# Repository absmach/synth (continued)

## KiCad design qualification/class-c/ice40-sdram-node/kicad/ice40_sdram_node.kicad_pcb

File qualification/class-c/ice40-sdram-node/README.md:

# iCE40HX4K SDR SDRAM node with a USB-C power input (Class C, case 2)

An iCE40HX4K FPGA in a 144-pin TQFP (0.5 mm pitch) with a 64 Mbit SDR SDRAM (ISSI IS42S16400J, TSOP-II-54), an SPI boot flash, a 1x6 programming header and three status LEDs. A USB-C receptacle (5 V only) powers it. The board has six copper layers and measures 70.0 x 61.0 mm.

It answers #329 under #40: a board whose memory interface is length- and impedance-sensitive, made by an agent driving `synth mcp`. A soft controller in the FPGA fabric drives a single-data-rate SDRAM, so there is no DQS strobe, no differential pair and no DDR claim. Case 2 is claimed for the routing of the memory lines (length, skew, impedance) only. No controller or bitstream has run on the board, so no interface timing (setup, hold, 143 MHz operation) is claimed.

The prompt to reproduce the board is in [`PROMPT.md`](PROMPT.md), written from the finished board. The prompts the agent ran are in the history at `9f458a8d`.

## The board

### Parts

| Group         | Parts                                                                                                                                                              |
| ------------- | ------------------------------------------------------------------------------------------------------------------------------------------------------------------ |
| Power entry   | `J1` Korean Hroparts TYPE-C-31-M-12 USB-C receptacle. It takes 5 V from VBUS only. D+, D- and SBU are unconnected.                                                 |
| Power entry   | `R2` and `R3`, 5.1 k pull-downs on CC1 and CC2.                                                                                                                    |
| Power entry   | `F1` Bourns MF-MSMF110/16-2 (1.1 A hold, 2.2 A trip, 16 V).                                                                                                        |
| Power entry   | `D1` Nexperia PTVS6V0S1UR (6.0 V standoff, 6.67 V minimum breakdown), above the 5.25 V maximum input, and `C1`.                                                    |
| Power entry   | No reverse-polarity stage. A Type-C receptacle cannot be mated reversed.                                                                                           |
| 3.3 V         | `U1` Diodes AP7361C-33E-13 low-dropout regulator (1 A, 360 mV typical dropout at 1 A, SOT-223, stable with ceramic capacitors) with 10 uF capacitors `C2` to `C5`. |
| 3.3 V         | `R_SURGE`, a 1 ohm series resistor (Yageo RC1206FR-071RL, 250 mW) that keeps a clamp event of `D1` off the regulator input.                                        |
| 1.2 V core    | `U2` Texas Instruments TLV70012DDCR, TSOT-23-5, with `C6` and `C7`.                                                                                                |
| 1.2 V core    | The PLL supply `VCCPLL` runs through the ferrite bead `L1` (Murata BLM18AG601SN1D) and `C23`.                                                                      |
| FPGA          | `U3` Lattice iCE40HX4K-TQ144 with 100 nF supply decoupling `C10` to `C24`.                                                                                         |
| FPGA          | `X1`, a 25 MHz oscillator on global buffer input `GBIN1` (`iot_197_gbin1`) with `C41`. The iCE40HX has no internal oscillator.                                     |
| FPGA          | `RCB1` and `RCB2` pull `CBSEL0` and `CBSEL1` down.                                                                                                                 |
| SDRAM         | `U4` ISSI IS42S16400J-7TLI (64 Mbit, 143 MHz, 3.0 to 3.6 V) with decoupling `C30` to `C37`.                                                                        |
| SDRAM         | Six 22 ohm series resistors `RS1` to `RS6` at the FPGA end of the command, clock and control lines.                                                                |
| SDRAM         | `RPD1` to `RPD8`, one 10 k resistor from each of `DQ0` to `DQ7` to ground.                                                                                         |
| Configuration | `U5` Winbond W25Q128JVSIQ, SOIC-8 208 mil, master SPI.                                                                                                             |
| Configuration | `R10` and `R11` pull `CRESET_B` and `CDONE` up. `R12` pulls up the chip select. `R13` and `R14` pull up the write-protect and hold pins.                           |
| Configuration | `J2` 1x6 programming header (SS_B, SCK, SDI, SDO, CRESET_B, GND).                                                                                                  |
| Protection    | `D6` and `D7` TPD1E10B06 bidirectional TVS diodes, one on each CC line at the receptacle, with no rail connection.                                                 |
| Indicators    | `D2` red (3.3 V present).                                                                                                                                          |
| Indicators    | `D3` green (CDONE), buffered by the N-MOSFET `Q2` AO3400A because CDONE is open-drain.                                                                             |
| Indicators    | `D4` green user LED.                                                                                                                                               |
| Mechanical    | Test points `TP1` to `TP7`, all on the bottom side of the board. `TP1` to `TP6` sit in a row 1.3 mm from the bottom edge.                                                                                                                                        |
| Mechanical    | Two M2.5 mounting holes `H1` and `H2` at opposite corners, each 4.0 mm from its two board edges.                                                                                                         |

### Layout

| Item                    | Value                                                                                                                                                                                         |
| ----------------------- | --------------------------------------------------------------------------------------------------------------------------------------------------------------------------------------------- |
| Outline                 | 70.0 x 61.0 mm                                                                                                                                                                                |
| Copper layers           | 6                                                                                                                                                                                             |
| Stackup                 | JLCPCB `JLC06161H-3313`: prepreg 3313 0.0994 mm er 4.1, core 0.55 mm er 4.6, prepreg 2116 0.1088 mm er 4.16. Outer copper 35 um, inner 15.2 um. The board is 1.47 mm thick in the STEP model. |
| Parts in the BOM        | 85 lines: 76 parts plus 2 mounting holes and 7 test points, which are board features with no part                                                                                             |
| Parts placed in the CPL | 76                                                                                                                                                                                            |
| Nets                    | 69, all 69 routed                                                                                                                                                                             |
| Track segments          | 913                                                                                                                                                                                           |
| Vias                    | 197: 78 of 0.46/0.2 mm and 119 of 0.6/0.3 mm                                                                                                                                                  |
| Track length            | 1874.2 mm                                                                                                                                                                                     |
| Zones and planes        | A `GND` zone on all six layers. Supply nets are routed as tracks.                                                                                                                             |
| Fab package             | `fab/gerbers.zip` (18 files: 13 Gerber layers, two drill files, two drill maps and the job file), `fab/bom.csv` and `fab/cpl.csv`                                                             |
| 3D models               | `models/` holds the STEP body of every part the board references and the board model `ice40_sdram_node.step`. KiCad's library has no model for `J1` or `X1`. `J1` uses the HRO TYPE-C-31-M-12 STEP from github.com/ai03-2725/Type-C.pretty (the repository states no licence), placed to match KiCad's footprint. `X1` is a simplified box of its envelope. The mounting holes have no body. The board file reaches the models by the relative path `${KIPRJMOD}/../models/`. |
| Schematic               | `images/schematic.pdf`: 11 vector pages, one per sheet, plotted by `kicad-cli sch export pdf`.                                                                                                               |

### Checks

| Check                               | Result                               | Notes                                                                                                                                                                         |
| ----------------------------------- | ------------------------------------ | ----------------------------------------------------------------------------------------------------------------------------------------------------------------------------- |
| KiCad DRC (10.0.8, --refill-zones)  | 0 errors, 1 warning, 0 unconnected  | The warning is a `via_dangling` on a `CRESET_B` via beside `TP6`. The DRC without `--refill-zones` reports the same.                                                                                                 |
| KiCad ERC (10.0.8)                  | 0 errors, 18 warnings, 0 unconnected | 17 `lib_symbol_issues` and 1 `lib_symbol_mismatch` warnings.                                                                                                                  |
| Gerbers plotted from refilled zones | Yes                                  | The committed board carries refilled zones, and the Gerbers are plotted from that fill.                                                                                       |
| Routing                             | 69 of 69 nets routed                 | KiCadRoutingTools `9399bfb2`.                                                                                                                                                 |
| Routing engine policy               | `engine_policy_verdict: rejected`    | Its strict-size policy rejects any track or via narrower than its net class. Its counters claim 172 vias and 0 in pads. The Layout counts are taken from the delivered board. |
| Synth validate                      | No errors                            | It reports `W-SYNTH-THERMAL-001` on `Q2`. The check applies the generic AO3400A package rating to an LED switch, not a real load.                                             |
| Class skew check `E-SYNTH-DRC-019`  | Not run                              | Synth's export gate does not run it (#147). The skew figures below are measured on the delivered board.                                                                       |

### Design figures

| Area             | Item                                               | Value                                                                                                                                                                                                                                    | Basis                                                      |
| ---------------- | -------------------------------------------------- | ---------------------------------------------------------------------------------------------------------------------------------------------------------------------------------------------------------------------------------------- | ---------------------------------------------------------- |
| FPGA             | User I/O                                           | 107                                                                                                                                                                                                                                      | Lattice DS1040                                             |
| FPGA             | Part model                                         | [`registry/parts/fpga/ice40hx4k_tq144.synth.toml`](../../../registry/parts/fpga/ice40hx4k_tq144.synth.toml), built from KiCad's `FPGA_Lattice:ICE40HX4K-TQ144` symbol with the pin functions of DS1040                                   | Lattice DS1040                                             |
| FPGA             | `GNDPLL` pins `gndpll0` and `gndpll1` | Left unconnected. Lattice DS1040 v3.4, Signal Descriptions: the PLL ground connection is made on the FPGA, so `GNDPLL` must not be connected to the board ground. The PLL is not used. | Lattice DS1040 v3.4 |
| Placement        | Memory pins                                        | The memory pins sit on the FPGA's left side facing the SDRAM, in the order of the SDRAM's near pin row. The data bus runs straight across with no crossings.                                                                             | measured on the board file                                 |
| Signal integrity | Address and command skew                           | 57.6 mm, limit `max_skew` 60 mm                                                                                                                                                                                                          | measured on the board file                                 |
| Signal integrity | Longest address or command net                     | `SD_RAS`, 68.6 mm across both nets of its series resistor, limit `max_length` 80 mm                                                                                                                                                       | measured on the board file                                 |
| Signal integrity | Shortest address or command net                    | `SD_A7`, 11.0 mm                                                                                                                                                                                                                        | measured on the board file                                 |
| Signal integrity | Data bus spread                                    | 6.3 mm, limit `max_skew` 10 mm                                                                                                                                                                                                           | measured on the board file                                 |
| Signal integrity | Data bus lengths, `DQ8` to `DQ15`                  | 14.0, 13.7, 11.5, 17.7, 11.6, 12.0, 14.1, 12.3 mm, limit `max_length` 60 mm                                                                                                                                                              | measured on the board file                                 |
| Signal integrity | `SD_CK` length                                     | 16.9 mm: 10.1 mm to the series resistor and 6.8 mm beyond it, limit `max_length` 40 mm                                                                                                                                                   | measured on the board file                                 |
| Signal integrity | SDRAM timing window                                | 7 ns minimum clock cycle (143 MHz), address and command setup 1.5 ns, hold 0.8 ns. This leaves a 4.7 ns window.                                                                                                                          | ISSI IS42S16400J Rev. G, AC Characteristics, CAS latency 3 |
| Signal integrity | Skew budget                                        | At 7.0 ps/mm (stripline, er 4.4), 60 mm of skew is 0.42 ns, 8.9 % of the window. The delivered 57.6 mm is 0.40 ns, 8.6 %.                                                                                                                | calculated                                                 |
| Signal integrity | Longest-run delay                                  | An 80 mm run is 0.56 ns of delay.                                                                                                                                                                                                        | calculated                                                 |
| Signal integrity | `SDCLK` impedance                                  | Declared 50 ohm. A 0.15 mm outer track over 0.0994 mm of prepreg gives Z0 = 87/sqrt(er+1.41) x ln(5.98 h / (0.8 w + t)) = 49.8 ohm. This is a closed-form microstrip estimate, not a field solve.                                        | calculated                                                 |
| Signal integrity | Data and address impedance                         | No target. The AC characteristics give timing only. The nets are LVTTL with 22 ohm series resistors, and 0.15 mm is the class width on every layer.                                                                                      | ISSI IS42S16400J Rev. G, AC Characteristics                |
| Signal integrity | Data bus byte                                      | The board uses the upper byte, `DQ8` to `DQ15`, the pin row that faces the FPGA. The FPGA holds `SD_LDQM` high, which masks the lower byte.                                                                                              | ISSI IS42S16400J Rev. G                                    |
| Signal integrity | Lower byte                                         | `DQ0` to `DQ7` each go to ground through their own 10 k resistor, so no two outputs share a net. The SDRAM ignores a masked byte on a write and keeps it high-impedance on a read.                                                       | ISSI IS42S16400J Rev. G                                    |
| Signal integrity | Edge rate, `SDDATA` and `SDCLK`                    | `fast`, because the SDRAM drives the data bus on a read and no output-edge figure for the IS42S16400J was found.                                                                                                                         | ISSI IS42S16400J Rev. G                                    |
| Signal integrity | Edge rate, `SDADDR`                                | `medium`. Only the FPGA drives it. The fast-corner 20 to 80 % edges are at least 0.976 ns (banks 0 to 2) and 0.728 ns (bank 3).                                                                                                          | Lattice IBIS model `ice40.ibs` rev 2.5                     |
| Signal integrity | Return-via window, medium edge                     | 6 mm                                                                                                                                                                                                                                     | #445                                                       |
| Signal integrity | Nearest ground via, `SD_DQ` (10 vias)              | 0.60 to 0.72 mm, median 0.67 mm, centre to centre                                                                                                                                                                                        | measured on the board file                                 |
| Signal integrity | Nearest ground via, `SD_CK`, `SD_CK_F`, `SD_CKE` and `SD_CKE_F` (4 vias) | 0.67 to 3.79 mm, median 1.14 mm, centre to centre                                                                                                                                                                                        | measured on the board file                                 |
| Signal integrity | Nearest ground via, address and control (49 vias)  | 0.67 to 4.88 mm, median 2.06 mm, centre to centre                                                                                                                                                                                        | measured on the board file                                 |
| Power            | `U1` ratings                                       | 1 A, input 2.2 to 6.0 V recommended, 6.5 V absolute maximum, SOT-223 `RthJA` 110 degC/W. It carries every load on `+3V3`.                                                                                                                | Diodes DS37274 Rev. 5-2                                    |
| Power            | 3.3 V load, `U2` 1.2 V regulator                   | 28.7 mA: iCE40 core 22.3 mA plus PLL 6.4 mA                                                                                                                                                                                              | Lattice DS1040 v3.4, Peak Startup Supply Current, HX       |
| Power            | 3.3 V load, `U4` SDRAM                             | 90 mA, `Idd4` maximum (all banks, BL 4, CL 3)                                                                                                                                                                                            | ISSI IS42S16400J Rev. G, DC Electrical Characteristics 1   |
| Power            | 3.3 V load, `U3` I/O banks and SPI supply          | 34 mA: 6.8 mA each, five supplies                                                                                                                                                                                                        | Lattice DS1040 v3.4                                        |
| Power            | 3.3 V load, `U3` NVCM supply `VPP_2V5`             | 4.1 mA                                                                                                                                                                                                                                   | Lattice DS1040 v3.4                                        |
| Power            | 3.3 V load, `U5` flash                             | 25 mA, program and erase maximum                                                                                                                                                                                                         | Winbond W25Q128JV, DC Electrical Characteristics           |
| Power            | 3.3 V load, three LEDs                             | 10 mA: 3.3 V / 1 k each, ignoring the LED drop                                                                                                                                                                                           | calculated                                                 |
| Power            | 3.3 V load, `X1` oscillator                        | 4.5 mA, at 20 MHz with no load                                                                                                                                                                                                           | SiT8008B Rev. 1.07                                         |
| Power            | 3.3 V total                                        | 196.5 mA                                                                                                                                                                                                                                 | calculated                                                 |
| Power            | Regulator input                                    | At most 5.02 V at the 5.25 V maximum VBUS, through `R_SURGE`. At the 4.75 V minimum it is 4.52 V.                                                                                                                                        | calculated                                                 |
| Power            | Dropout margin                                     | 1.22 V above 3.3 V at the minimum input, against a 360 mV typical dropout at 1 A                                                                                                                                                         | calculated, Diodes DS37274 Rev. 5-2                        |
| Thermal          | Rated ambient                                      | 70 degC                                                                                                                                                                                                                                  | board rating                                               |
| Thermal          | `U1` dissipation                                   | (5.02 V - 3.3 V) x 0.192 A = 0.33 W, a 36 degC rise                                                                                                                                                                                      | calculated                                                 |
| Thermal          | `U1` junction temperature                          | 61 degC at 25 degC ambient, 106 degC at 70 degC                                                                                                                                                                                          | calculated                                                 |
| Thermal          | `U1` current limit at Tj 125 degC                  | 0.53 A in total at 25 degC, 0.29 A at 70 degC. At 70 degC this leaves about 0.10 A for the FPGA's dynamic current.                                                                                                                       | calculated                                                 |
| Thermal          | `U2` dissipation                                   | (3.3 V - 1.2 V) x 0.0287 A = 0.06 W                                                                                                                                                                                                      | calculated                                                 |
| Thermal          | `R_SURGE` dissipation                              | 0.037 W against a 250 mW rating                                                                                                                                                                                                          | calculated                                                 |
| Protection       | `D1` standoff                                      | 6.0 V, 0.75 V above the 5.25 V maximum VBUS, so it does not conduct in operation                                                                                                                                                         | Nexperia PTVS6V0S1UR datasheet                             |
| Protection       | `D1` clamp                                         | Up to 10.3 V at 38.8 A                                                                                                                                                                                                                   | Nexperia PTVS6V0S1UR datasheet                             |
| Protection       | Clamp-event current                                | `R_SURGE` limits the current into `C2` and `C3` (20 uF) to 5.8 A.                                                                                                                                                                        | calculated                                                 |
| Protection       | Clamp-event voltage                                | A 60 ns event raises `C2` and `C3` by 0.02 V and holds the regulator input near 5 V.                                                                                                                                                     | calculated                                                 |
| Protection       | Regulator choice                                   | Every low-dropout regulator considered (AP7361C, AP2114, AP2112K, LP5907) is rated 6.5 V or less at its input. Parts rated above the clamp (AMS1117-3.3, NCP1117) need an ESR-stabilised output capacitor, and this board uses ceramics. | regulator datasheets                                       |
| Assembly         | `J2` to `H2` keepout                               | The `J2` courtyard is 3.25 mm from the 5.5 mm screw-head keepout of `H2`.                                                                                                                                                                | measured on the board file                                 |
| Assembly         | `J2` to board edge                                 | `J2` sits on the bottom edge. Its pads are 0.92 mm inside the edge line, and its courtyard reaches 0.05 mm past it.                                                                                                                                                                               | measured on the board file                                 |

### Sourcing

| Item          | Status                                          | Notes                                          |
| ------------- | ----------------------------------------------- | ---------------------------------------------- |
| BOM           | 76 lines sourced, 9 board features with no part | Status as recorded in `fab/bom.csv`.           |
| Part pages    | Read in 2026-11                                 | Stock is not firm.                             |
| `D6` and `D7` | `TPD1E10B06DYAR`, LCSC `C3712135`               | The DYA package matches the SOD-523 footprint. |
| `J2`          | LCSC `C37208`                                   | Hand-fit through-hole part.                    |

## Not verified by Synth

| Area                 | What is not verified                                                                                                                                 |
| -------------------- | ---------------------------------------------------------------------------------------------------------------------------------------------------- |
| Interface timing     | No controller or bitstream has run on the board, so setup, hold and 143 MHz operation are not claimed.                                               |
| Return paths         | Three of the 4 clock-group vias are farther from a ground via than the 0.8 mm fast-net window. All 10 data vias are within it. The export lists 115 return-via advisories.                                                             |
| 3.3 V budget         | The FPGA's dynamic current depends on the bitstream and is not counted.                                                                              |
| 3.3 V budget         | The core and I/O figures are startup peaks for a blank pattern, and the I/O figure assumes 6.8 mA per supply.                                        |
| 3.3 V budget         | The oscillator figure is for the SiT8008B at 20 MHz, so it is indicative for the 25 MHz AI part.                                                     |
| Surge                | In a sustained over-voltage, `D1` holds its node near 7.0 V until `F1` opens. The regulator input then sees about 6.8 V, 0.3 V over its rating.      |
| Surge                | The pulse rating of `R_SURGE` was not read.                                                                                                          |
| SDRAM figures        | The IS42S16400J Rev. G figures were read from a mirror copy, because the ISSI-hosted PDF could not be retrieved. Check them against ISSI's own copy. |
| Sourcing             | Stock is not firm.                                                                                                                                   |
| Fabrication checks   | No JLCPCB DFM or BOM-matching run is recorded for this Gerber package.                                                                               |
| Independent sign-off | The independent PCB review required by #40 is still open.                                                                                            |

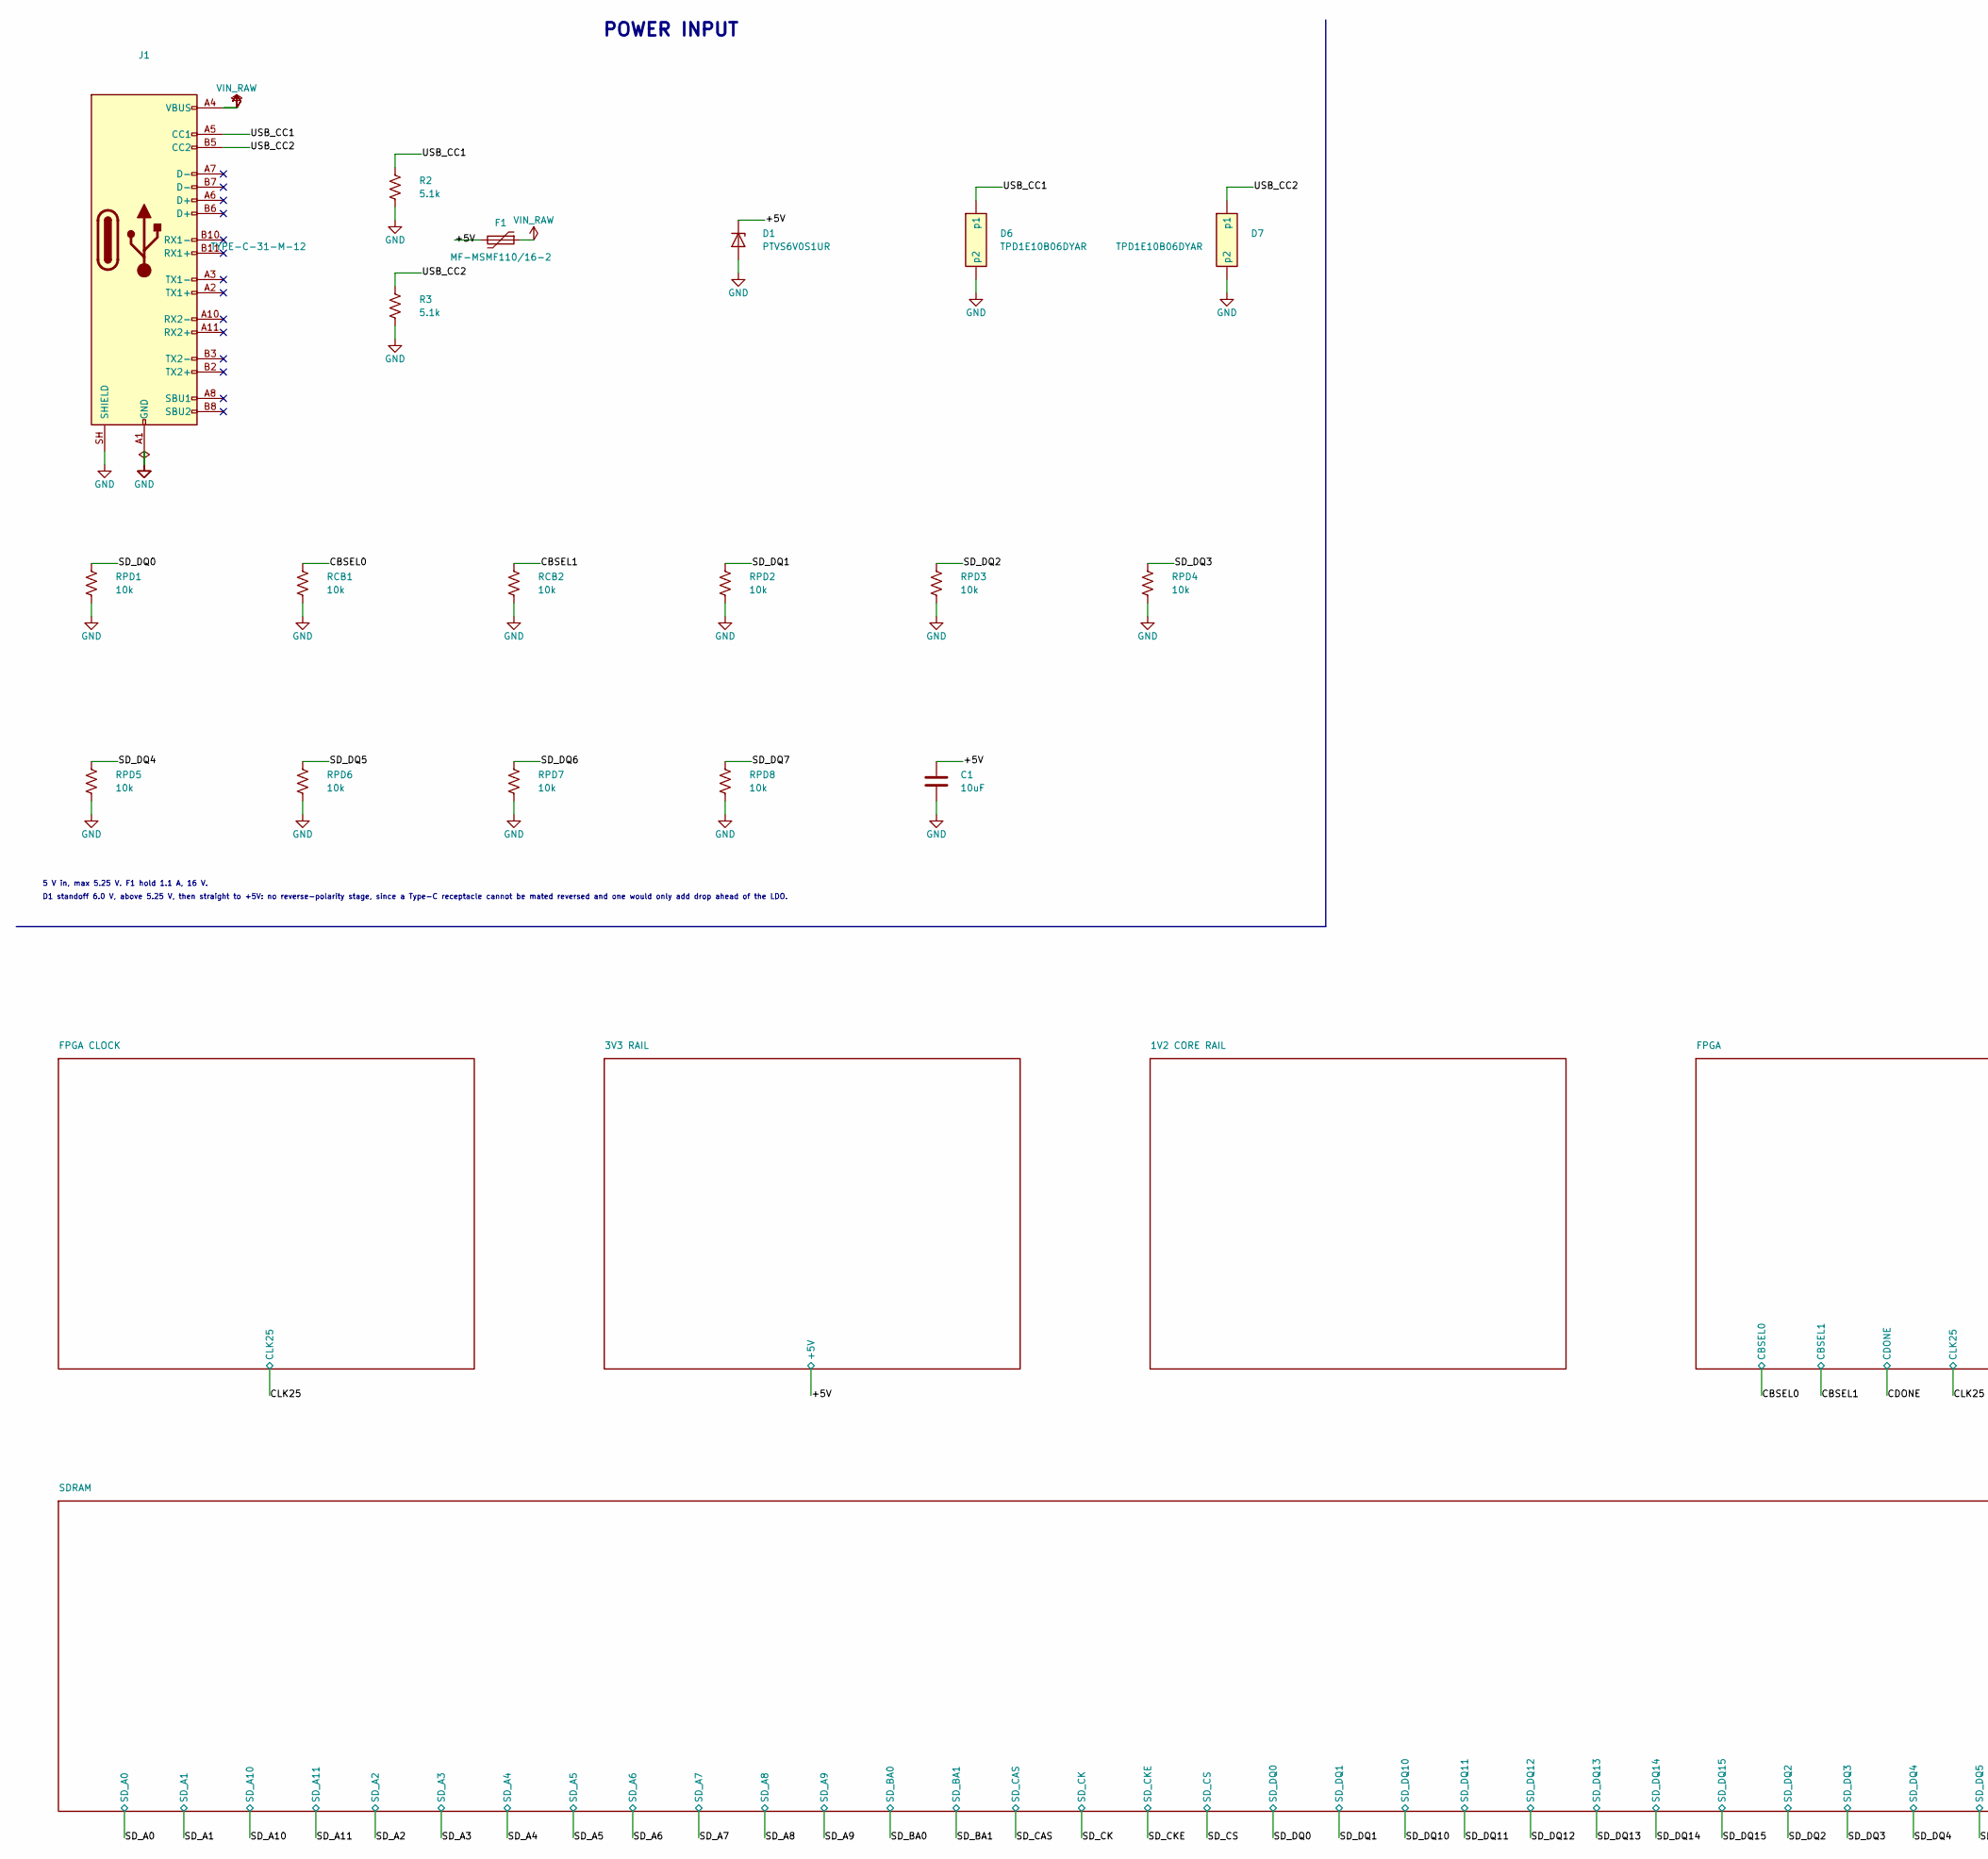
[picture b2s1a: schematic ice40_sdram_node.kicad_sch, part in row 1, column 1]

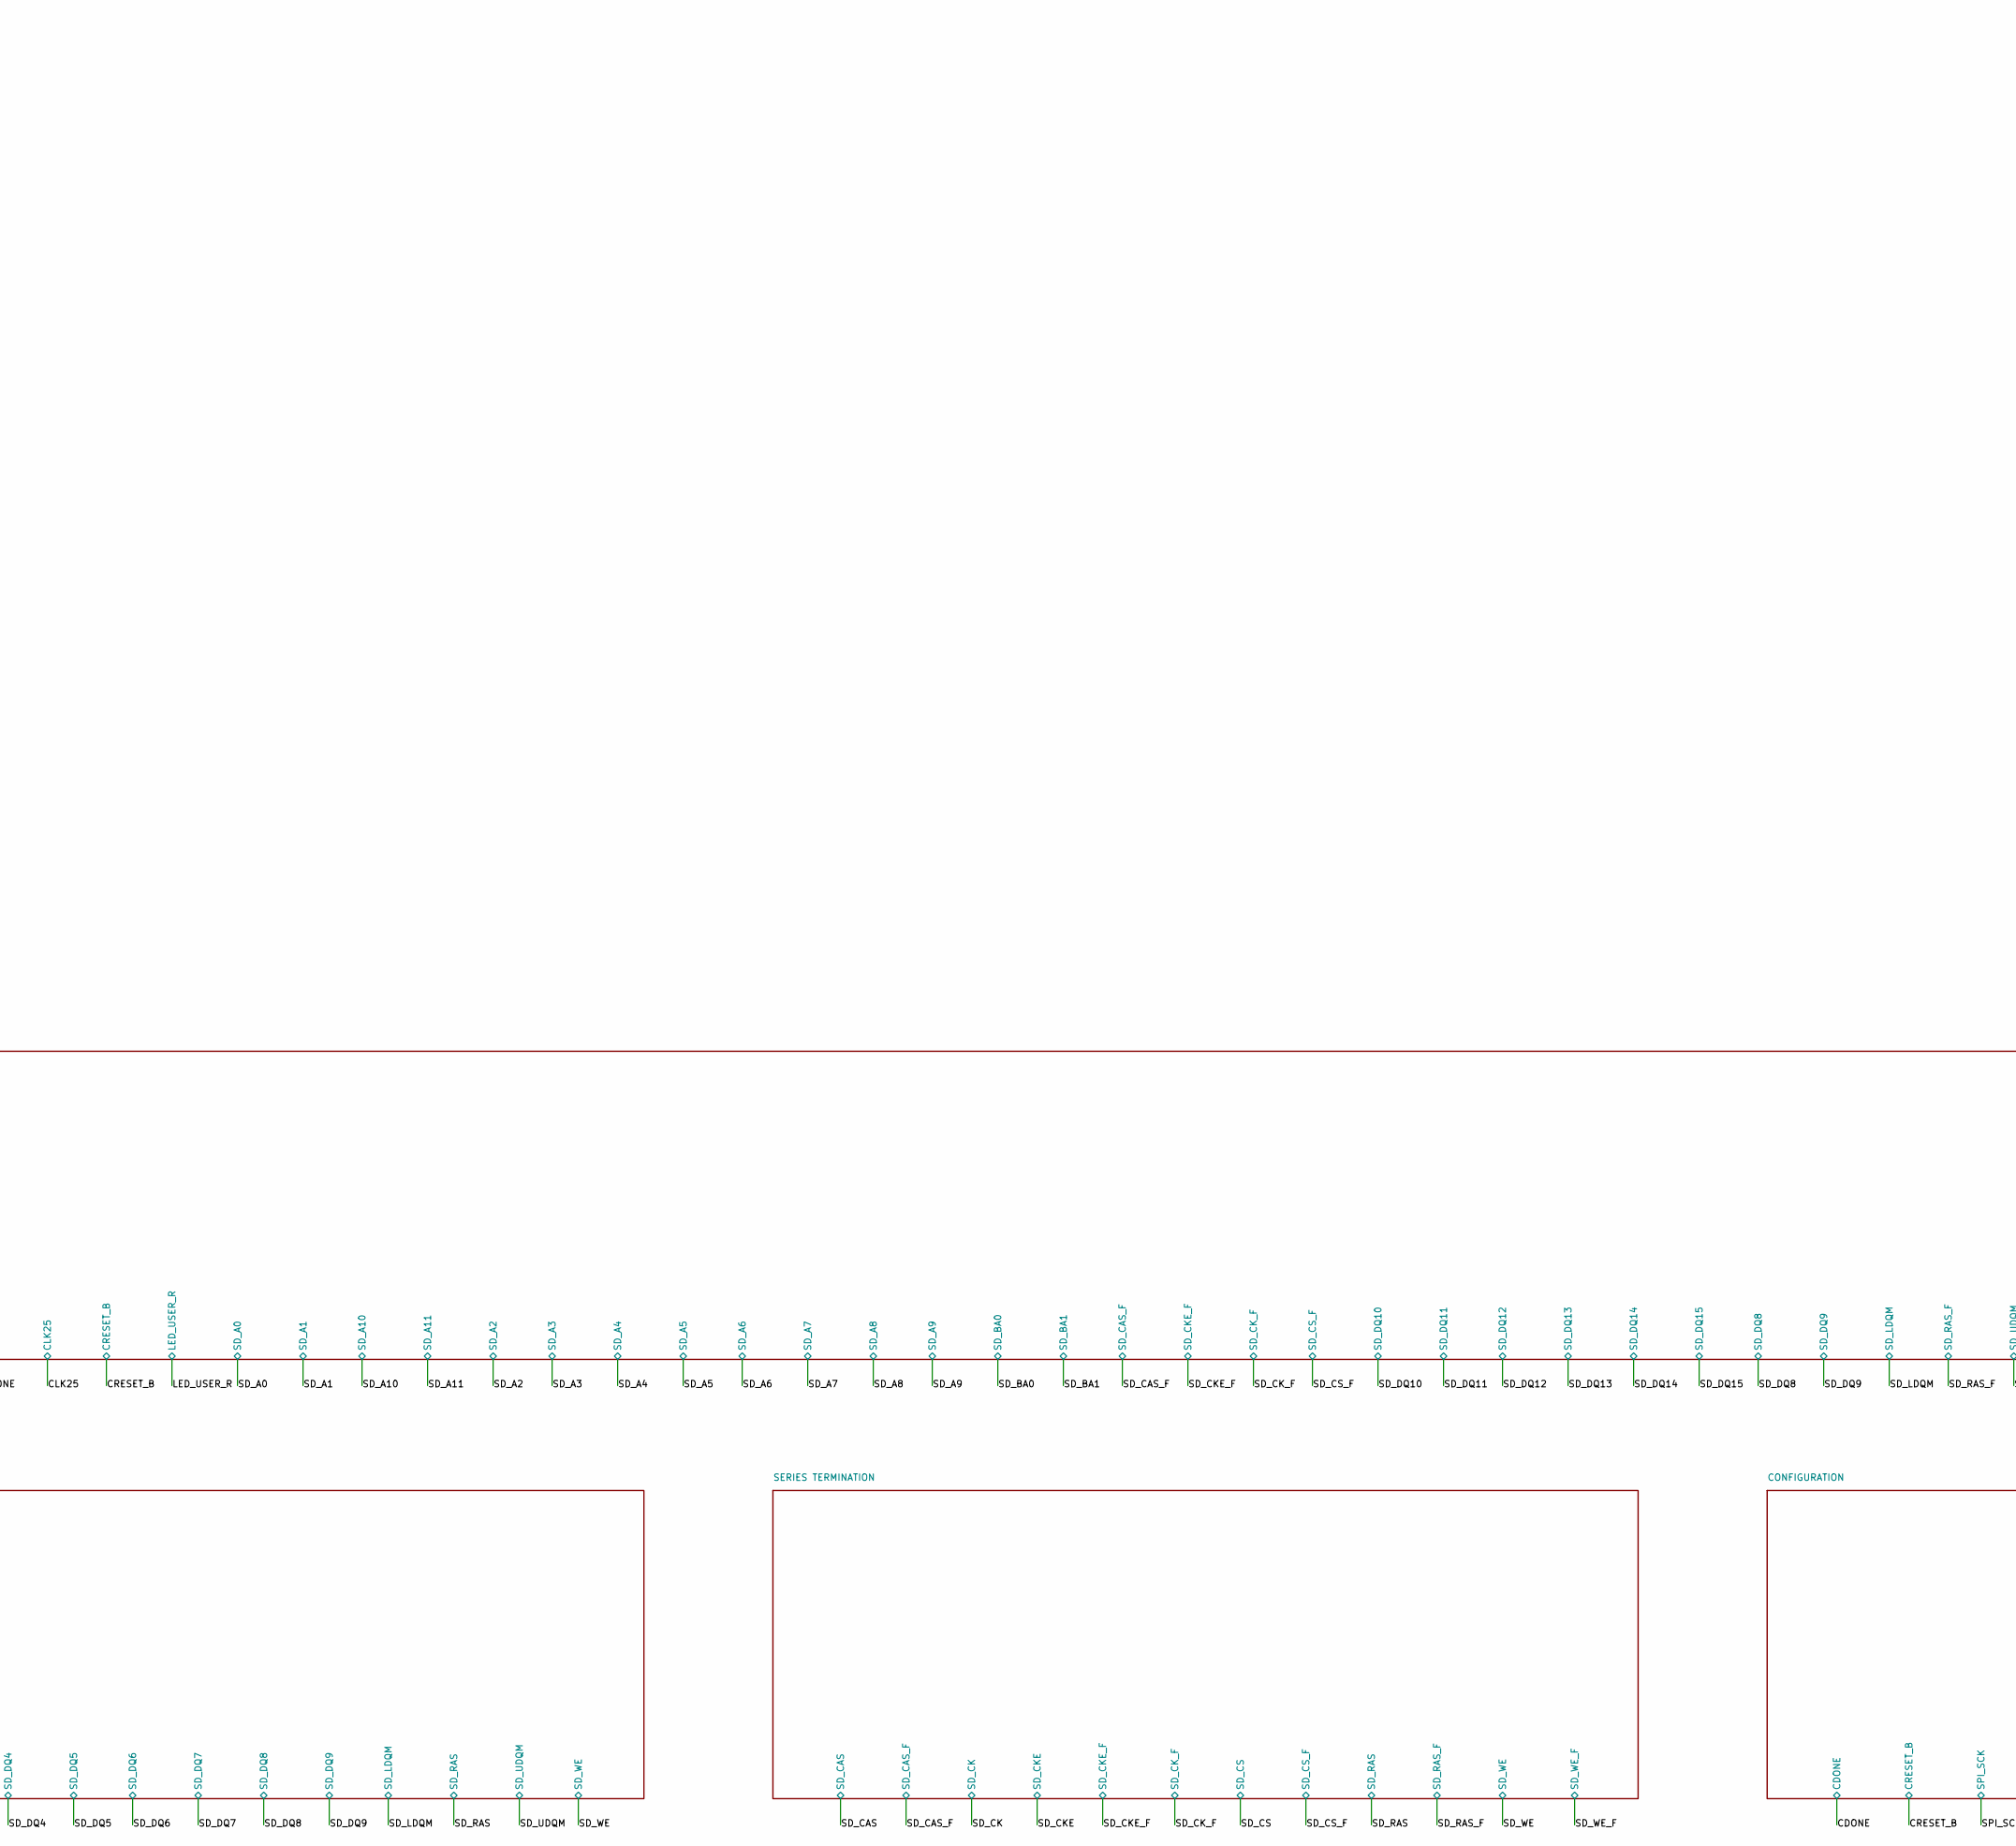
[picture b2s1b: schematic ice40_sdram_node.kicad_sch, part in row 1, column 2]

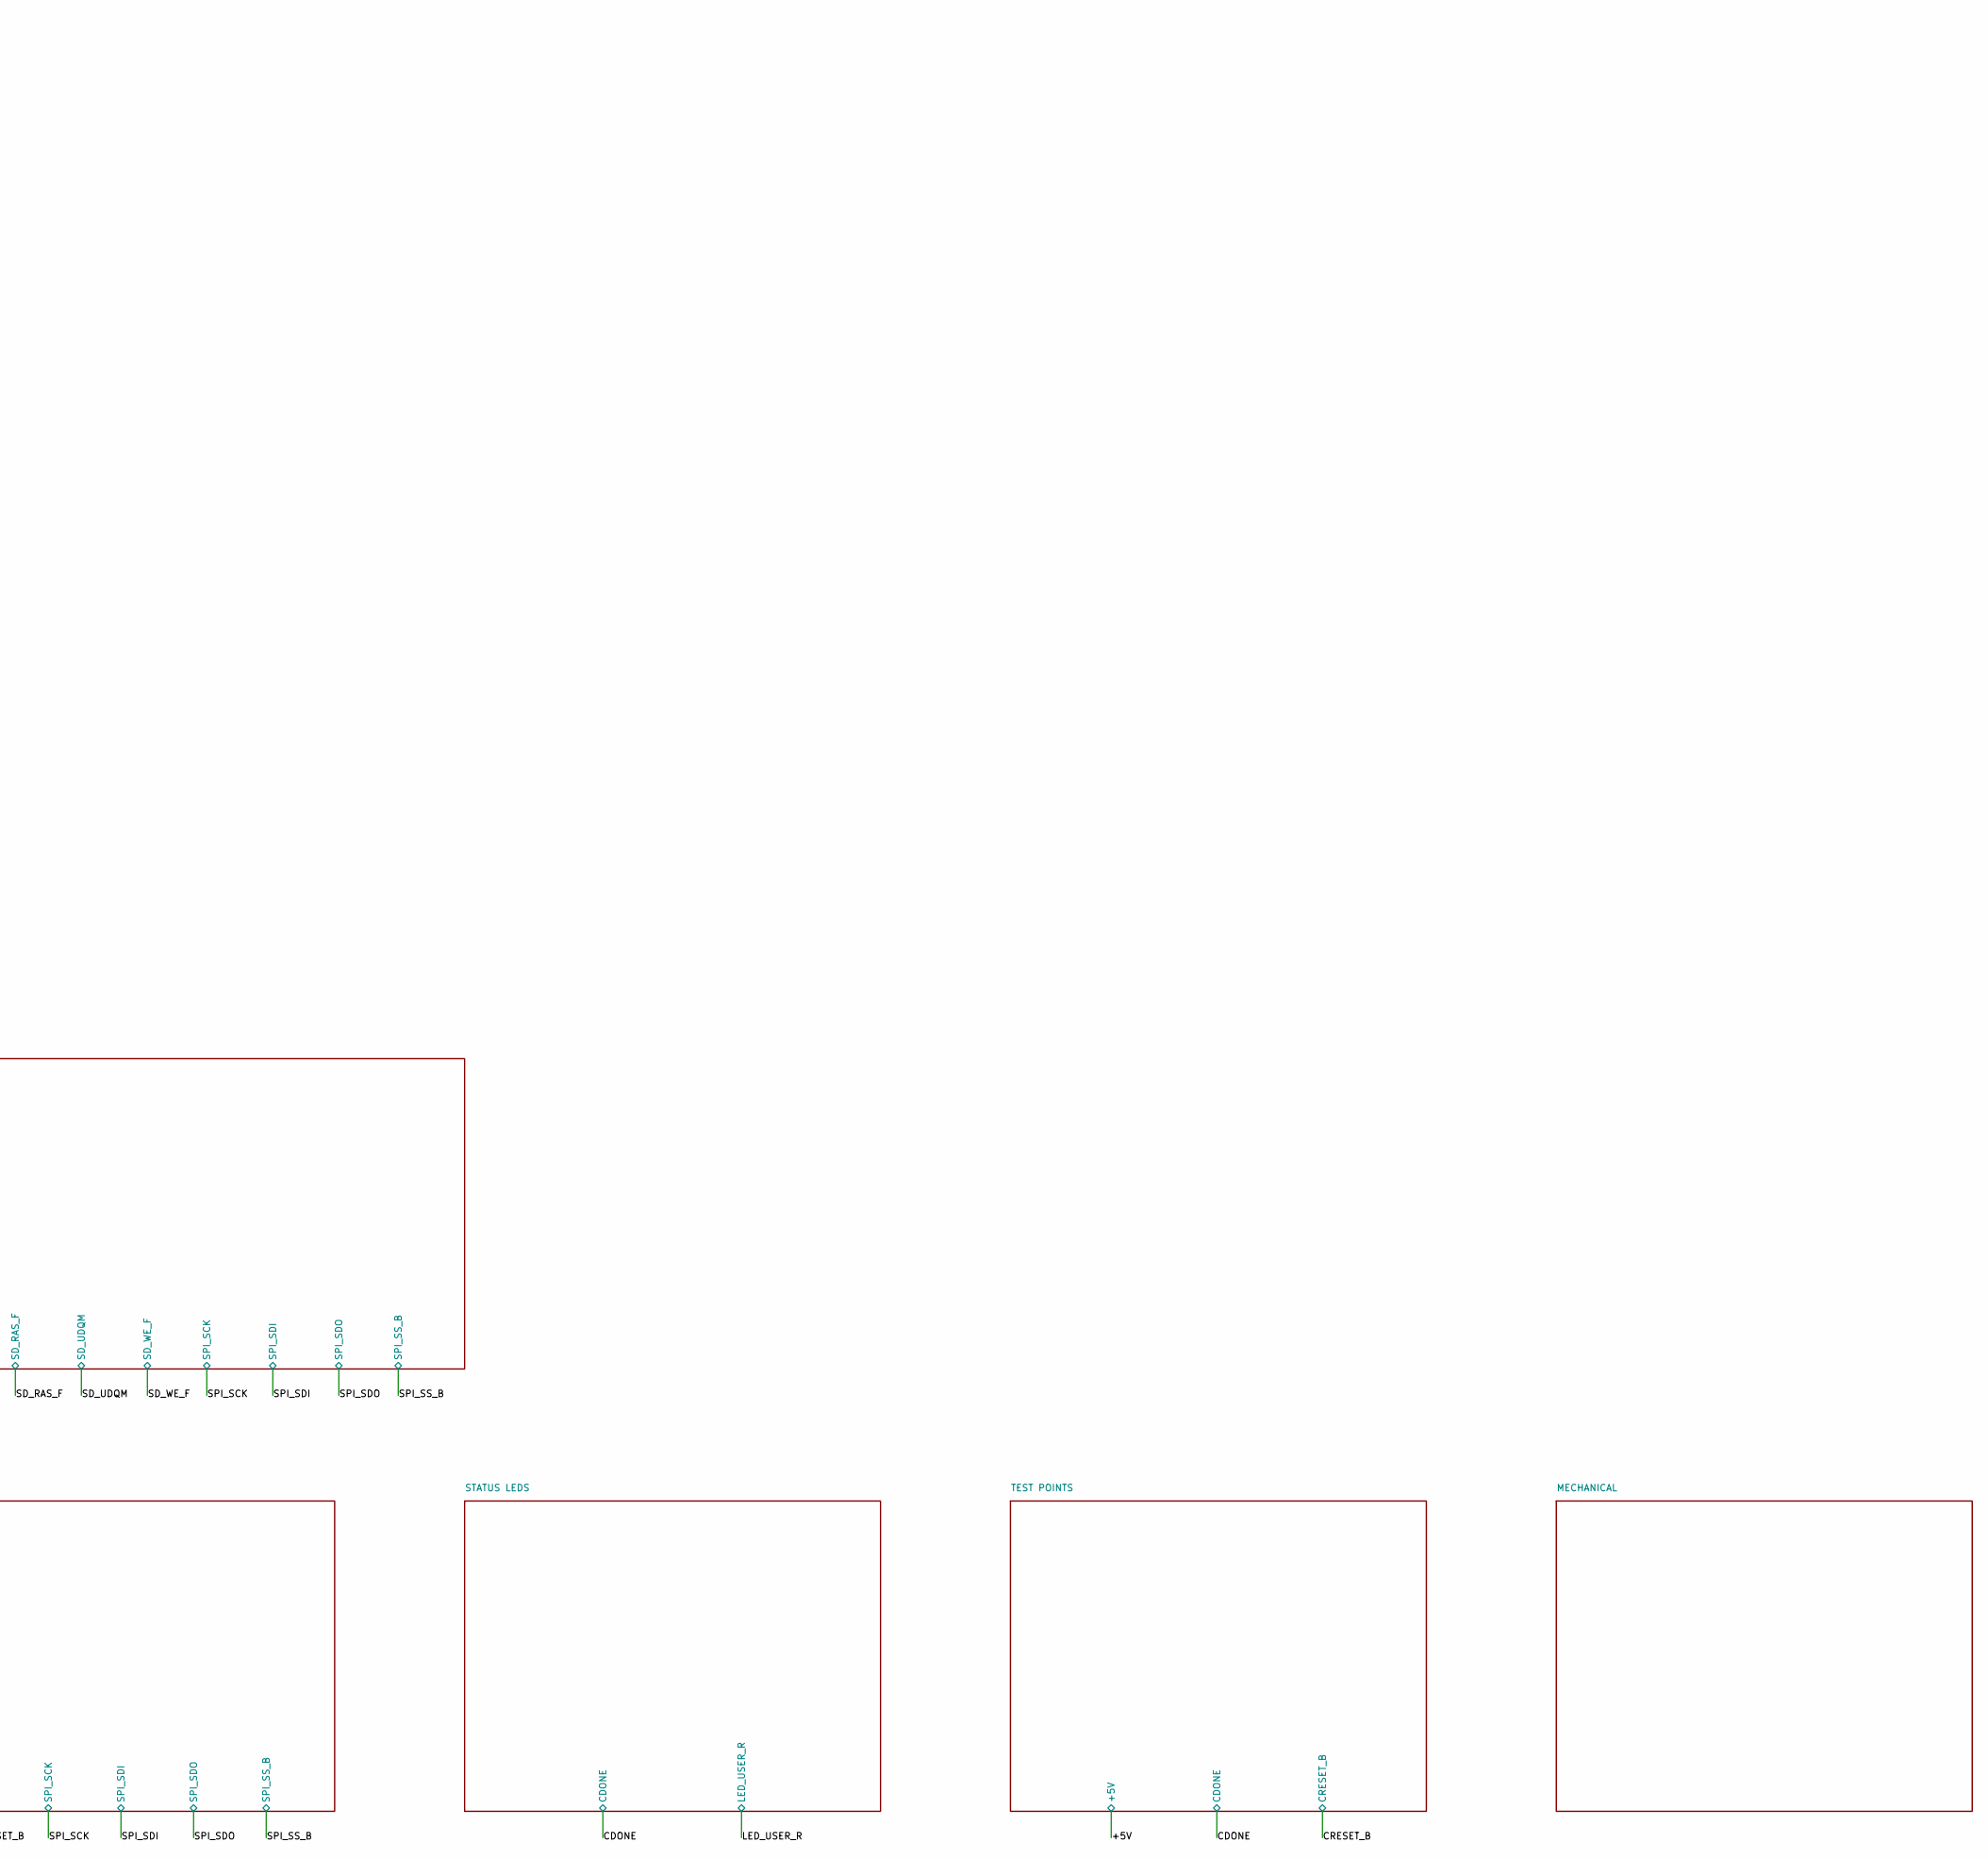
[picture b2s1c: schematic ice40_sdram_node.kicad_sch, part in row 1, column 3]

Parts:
C1: 10uF; C_0805_2012Metric
D1: PTVS6V0S1UR; Nexperia_CFP3_SOD-123W; MPN PTVS6V0S1UR
D6, D7: TPD1E10B06DYAR; D_SOD-523; MPN TPD1E10B06DYAR
F1: MF-MSMF110/16-2; Fuse_1812_4532Metric; MPN MF-MSMF110/16-2; LCSC C210834
J1: TYPE-C-31-M-12; USB_C_Receptacle_HRO_TYPE-C-31-M-12; MPN TYPE-C-31-M-12; LCSC C165948
R2, R3: 5.1k; R_0603_1608Metric
RCB1, RCB2: 10k; R_0402_1005Metric
RPD1: 10k; R_0603_1608Metric
RPD2, RPD3, RPD4, RPD5, RPD6, RPD7, RPD8: 10k; R_0402_1005Metric

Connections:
+5V: C1.1, D1.1 (K), F1.2; also elsewhere on the board
CBSEL0: RCB1.1; also elsewhere on the board
CBSEL1: RCB2.1; also elsewhere on the board
GND: C1.2, D1.2 (A), D6.2 (p2), D7.2 (p2), J1.A1 (GND), J1.A12 (GND), J1.B1 (GND), J1.B12 (GND), J1.SH (SHIELD), R2.2, R3.2, RCB1.2, RCB2.2, RPD1.2, RPD2.2, RPD3.2, RPD4.2, RPD5.2, RPD6.2, RPD7.2, RPD8.2; also elsewhere on the board
SD_DQ0: RPD1.1; also elsewhere on the board
SD_DQ1: RPD2.1; also elsewhere on the board
SD_DQ2: RPD3.1; also elsewhere on the board
SD_DQ3: RPD4.1; also elsewhere on the board
SD_DQ4: RPD5.1; also elsewhere on the board
SD_DQ5: RPD6.1; also elsewhere on the board
SD_DQ6: RPD7.1; also elsewhere on the board
SD_DQ7: RPD8.1; also elsewhere on the board
USB_CC1: D6.1 (p1), J1.A5 (CC1), R2.1
USB_CC2: D7.1 (p1), J1.B5 (CC2), R3.1
VIN_RAW: F1.1, J1.A4 (VBUS), J1.A9 (VBUS), J1.B4 (VBUS), J1.B9 (VBUS)

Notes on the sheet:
POWER INPUT
5 V in, max 5.25 V. F1 hold 1.1 A, 16 V.
D1 standoff 6.0 V, above 5.25 V, then straight to +5V: no reverse-polarity stage, since a Type-C receptacle cannot be mated reversed and one would only add drop ahead of the LDO.

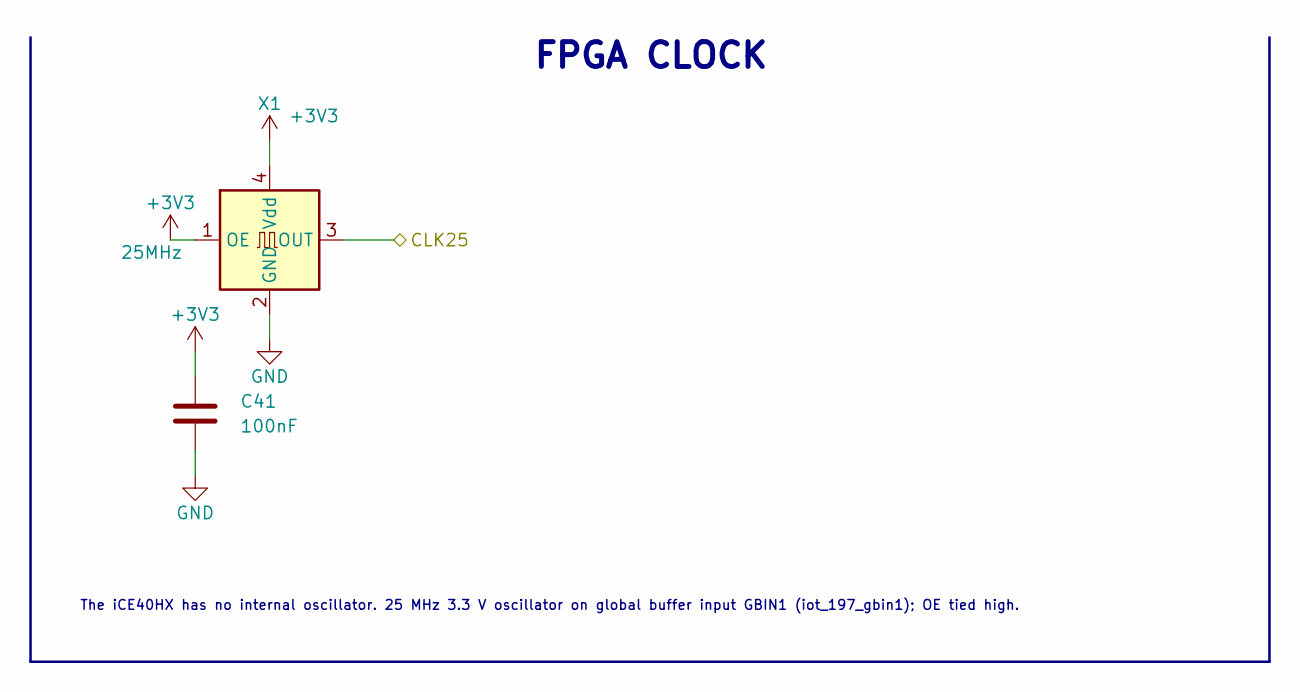
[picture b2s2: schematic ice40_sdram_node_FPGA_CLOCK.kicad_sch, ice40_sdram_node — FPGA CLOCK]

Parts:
C41: 100nF; C_0402_1005Metric
X1: 25MHz; Oscillator_SMD_SiT_PQFN-4Pin_5.0x3.2mm; MPN SiT8008AI-31-33S-25.000000; LCSC C826909

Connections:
+3V3: C41.1, X1.1 (OE), X1.4 (Vdd); also elsewhere on the board
CLK25: X1.3 (OUT); also elsewhere on the board
GND: C41.2, X1.2 (GND); also elsewhere on the board

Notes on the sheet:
FPGA CLOCK
The iCE40HX has no internal oscillator. 25 MHz 3.3 V oscillator on global buffer input GBIN1 (iot_197_gbin1); OE tied high.

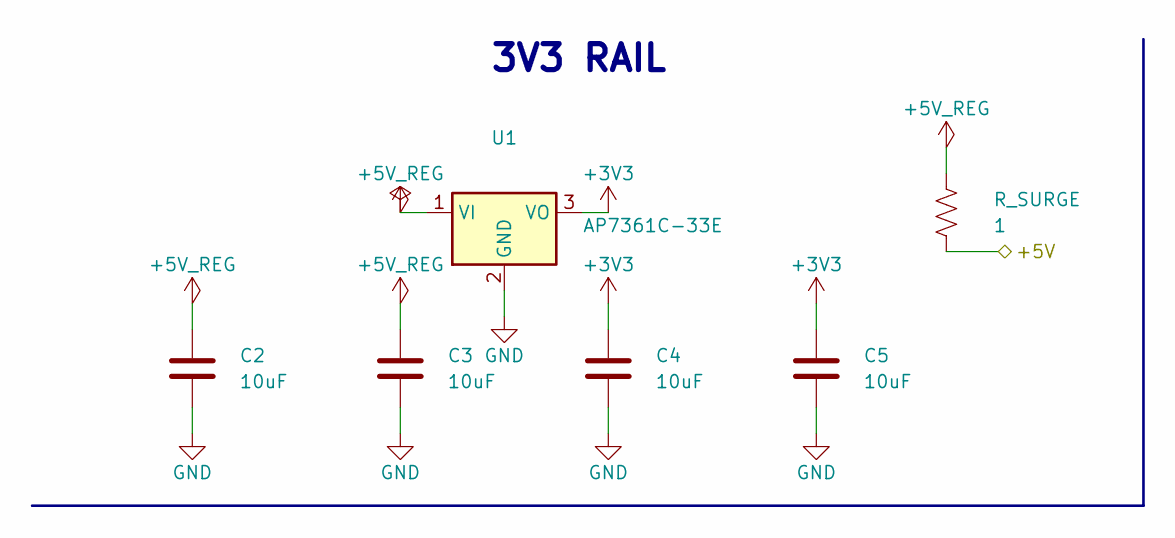
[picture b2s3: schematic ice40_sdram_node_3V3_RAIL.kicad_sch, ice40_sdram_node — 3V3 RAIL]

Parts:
C2, C3, C4, C5: 10uF; C_0805_2012Metric
R_SURGE: 1; R_1206_3216Metric
U1: AP7361C-33E; SOT-223-3_TabPin2; MPN AP7361C-33E-13; LCSC C500795

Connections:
+3V3: C4.1, C5.1, U1.3 (VO); also elsewhere on the board
+5V: R_SURGE.1; also elsewhere on the board
+5V_REG: C2.1, C3.1, R_SURGE.2, U1.1 (VI)
GND: C2.2, C3.2, C4.2, C5.2, U1.2 (GND); also elsewhere on the board

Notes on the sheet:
3V3 RAIL

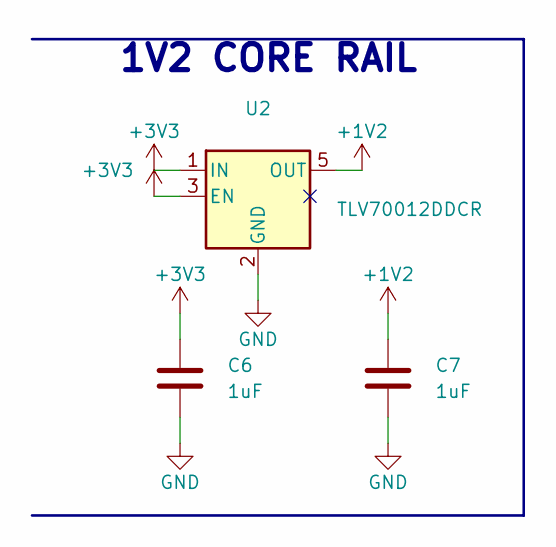
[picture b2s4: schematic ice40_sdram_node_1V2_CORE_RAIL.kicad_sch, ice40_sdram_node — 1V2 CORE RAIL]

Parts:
C6, C7: 1uF; C_0603_1608Metric
U2: TLV70012DDCR; TSOT-23-5; MPN TLV70012DDCR; LCSC C69446

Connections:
+1V2: C7.1, U2.5 (OUT); also elsewhere on the board
+3V3: C6.1, U2.1 (IN), U2.3 (EN); also elsewhere on the board
GND: C6.2, C7.2, U2.2 (GND); also elsewhere on the board

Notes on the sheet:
1V2 CORE RAIL
